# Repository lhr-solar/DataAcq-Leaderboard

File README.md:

# DataAcquisitionLeaderPCB

This PCB is designed for our solar vehicle to collect electrical and mechanical sensor data and transmit it wirelessly via LTE for real-time access. It also includes a GPS module for location tracking and an RF module as a backup communication system.

## LED Descriptions

LTE LEDs:

* HB (D7): Heartbeat.
  * Blinking = Our code is running on module.
* RSSI (D5): Received Singal Strength Integrity.
  * PWM based on strength (brighter = better).
* CONN (D4): Connection Indicator.
  * On, solid = Not connected.
  * 1/2 sec period blink = Last transmit failed.
  * 1 sec blink period = Normal operation.
* ON (D6): On.
  * On = Module is on.

RF LEDs:

* COM (D1): Commissioning (associate) status.
  * Blinking = Device is powered and operating properly.
  * Off = Device is alseep.
  * Note: blinks with certain patterns depending on number of RF_COM button presses (see datasheet).
* ON (D2): On.
  * On = Module is on.
* RSSI (D3): Received Singal Strength Integrity.
  * PWM based on strength (brighter = better).

GPS LED:

* NFX (D8): Negative 3D Fix.
  * Blinking (2 sec period) = Searching for satellites, no position fix.
  * Off = Acquired satellite signal.

## Testpoint Descriptions

LTE Testpoints:

* UART5 (J3)
  * Pin 3 TX = Transmit
  * Pin 2 RX = Receive
  * Pin 1 NR = Negative Reset (Note: this is not a UART singal, it is the module NRESET singal)

* Test Trace (J4)
  * Provides access to 4 pins (traces) to help in debugging code on the LTE module.

RF Testpoints:

* UART2 (J2)
  * Pin 3 TX = Transmit
  * Pin 2 RX = Receive
  * Pin 1 NR = Negative Reset (Note: this is not a UART singal, it is the module NRESET singal)

GPS Testpoints:

* I2C (J5)
  * Pin 3 SDA = Serial Data
  * Pin 2 SCL = Serial Clock
  * Pin 1 NR = Negative Reset (Note: this is not a I2C singal, it is the module NRESET singal)

## Pushbutton Descriptions

LTE_RESET: When pressed LTE module resets.
GPS_RESET: When pressed GPS module resets.
RF_RESET: When pressed RF module resets.
RF_COM: RF Commissioning button (see datasheet).

## PCB

## Schematic

[PDF](DataAcqLeaderBoard_Schematic.pdf)

## BOM

[BOM](DataAcqLeaderBoard/bom/bom.csv)
[IBOM](DataAcqLeaderBoard/bom/ibom.html)
[Mouser Cart](https://www.mouser.com/ProjectManager/ProjectDetail.aspx?AccessID=583e28cb45)

Cart does not include: 

  - [GPS Ferite Bead](https://www.digikey.com/en/products/detail/pulse-electronics/GMLB-100505-0600A-N8/12417638)
  - [GPS Module]( https://www.adafruit.com/product/790?gad_source=1&gclid=Cj0KCQiAsaS7BhDPARIsAAX5cSBvdF13g1xnso75e2ID2pkFIsjjoOZ1HywqQ3y7T4lSuiXb9zWTkFsaAgU-EALw_wcB)
  - [Digi XBee LTE Module](https://www.digi.com/products/embedded-systems/digi-xbee/cellular-modems/digi-xbee-3-global-lte-cat-4#partnumbers )
  - [Digi XBee RF Module](https://www.digi.com/products/embedded-systems/digi-xbee/rf-modules/sub-1-ghz-rf-modules/digi-xbee-xr-900#partnumbers)

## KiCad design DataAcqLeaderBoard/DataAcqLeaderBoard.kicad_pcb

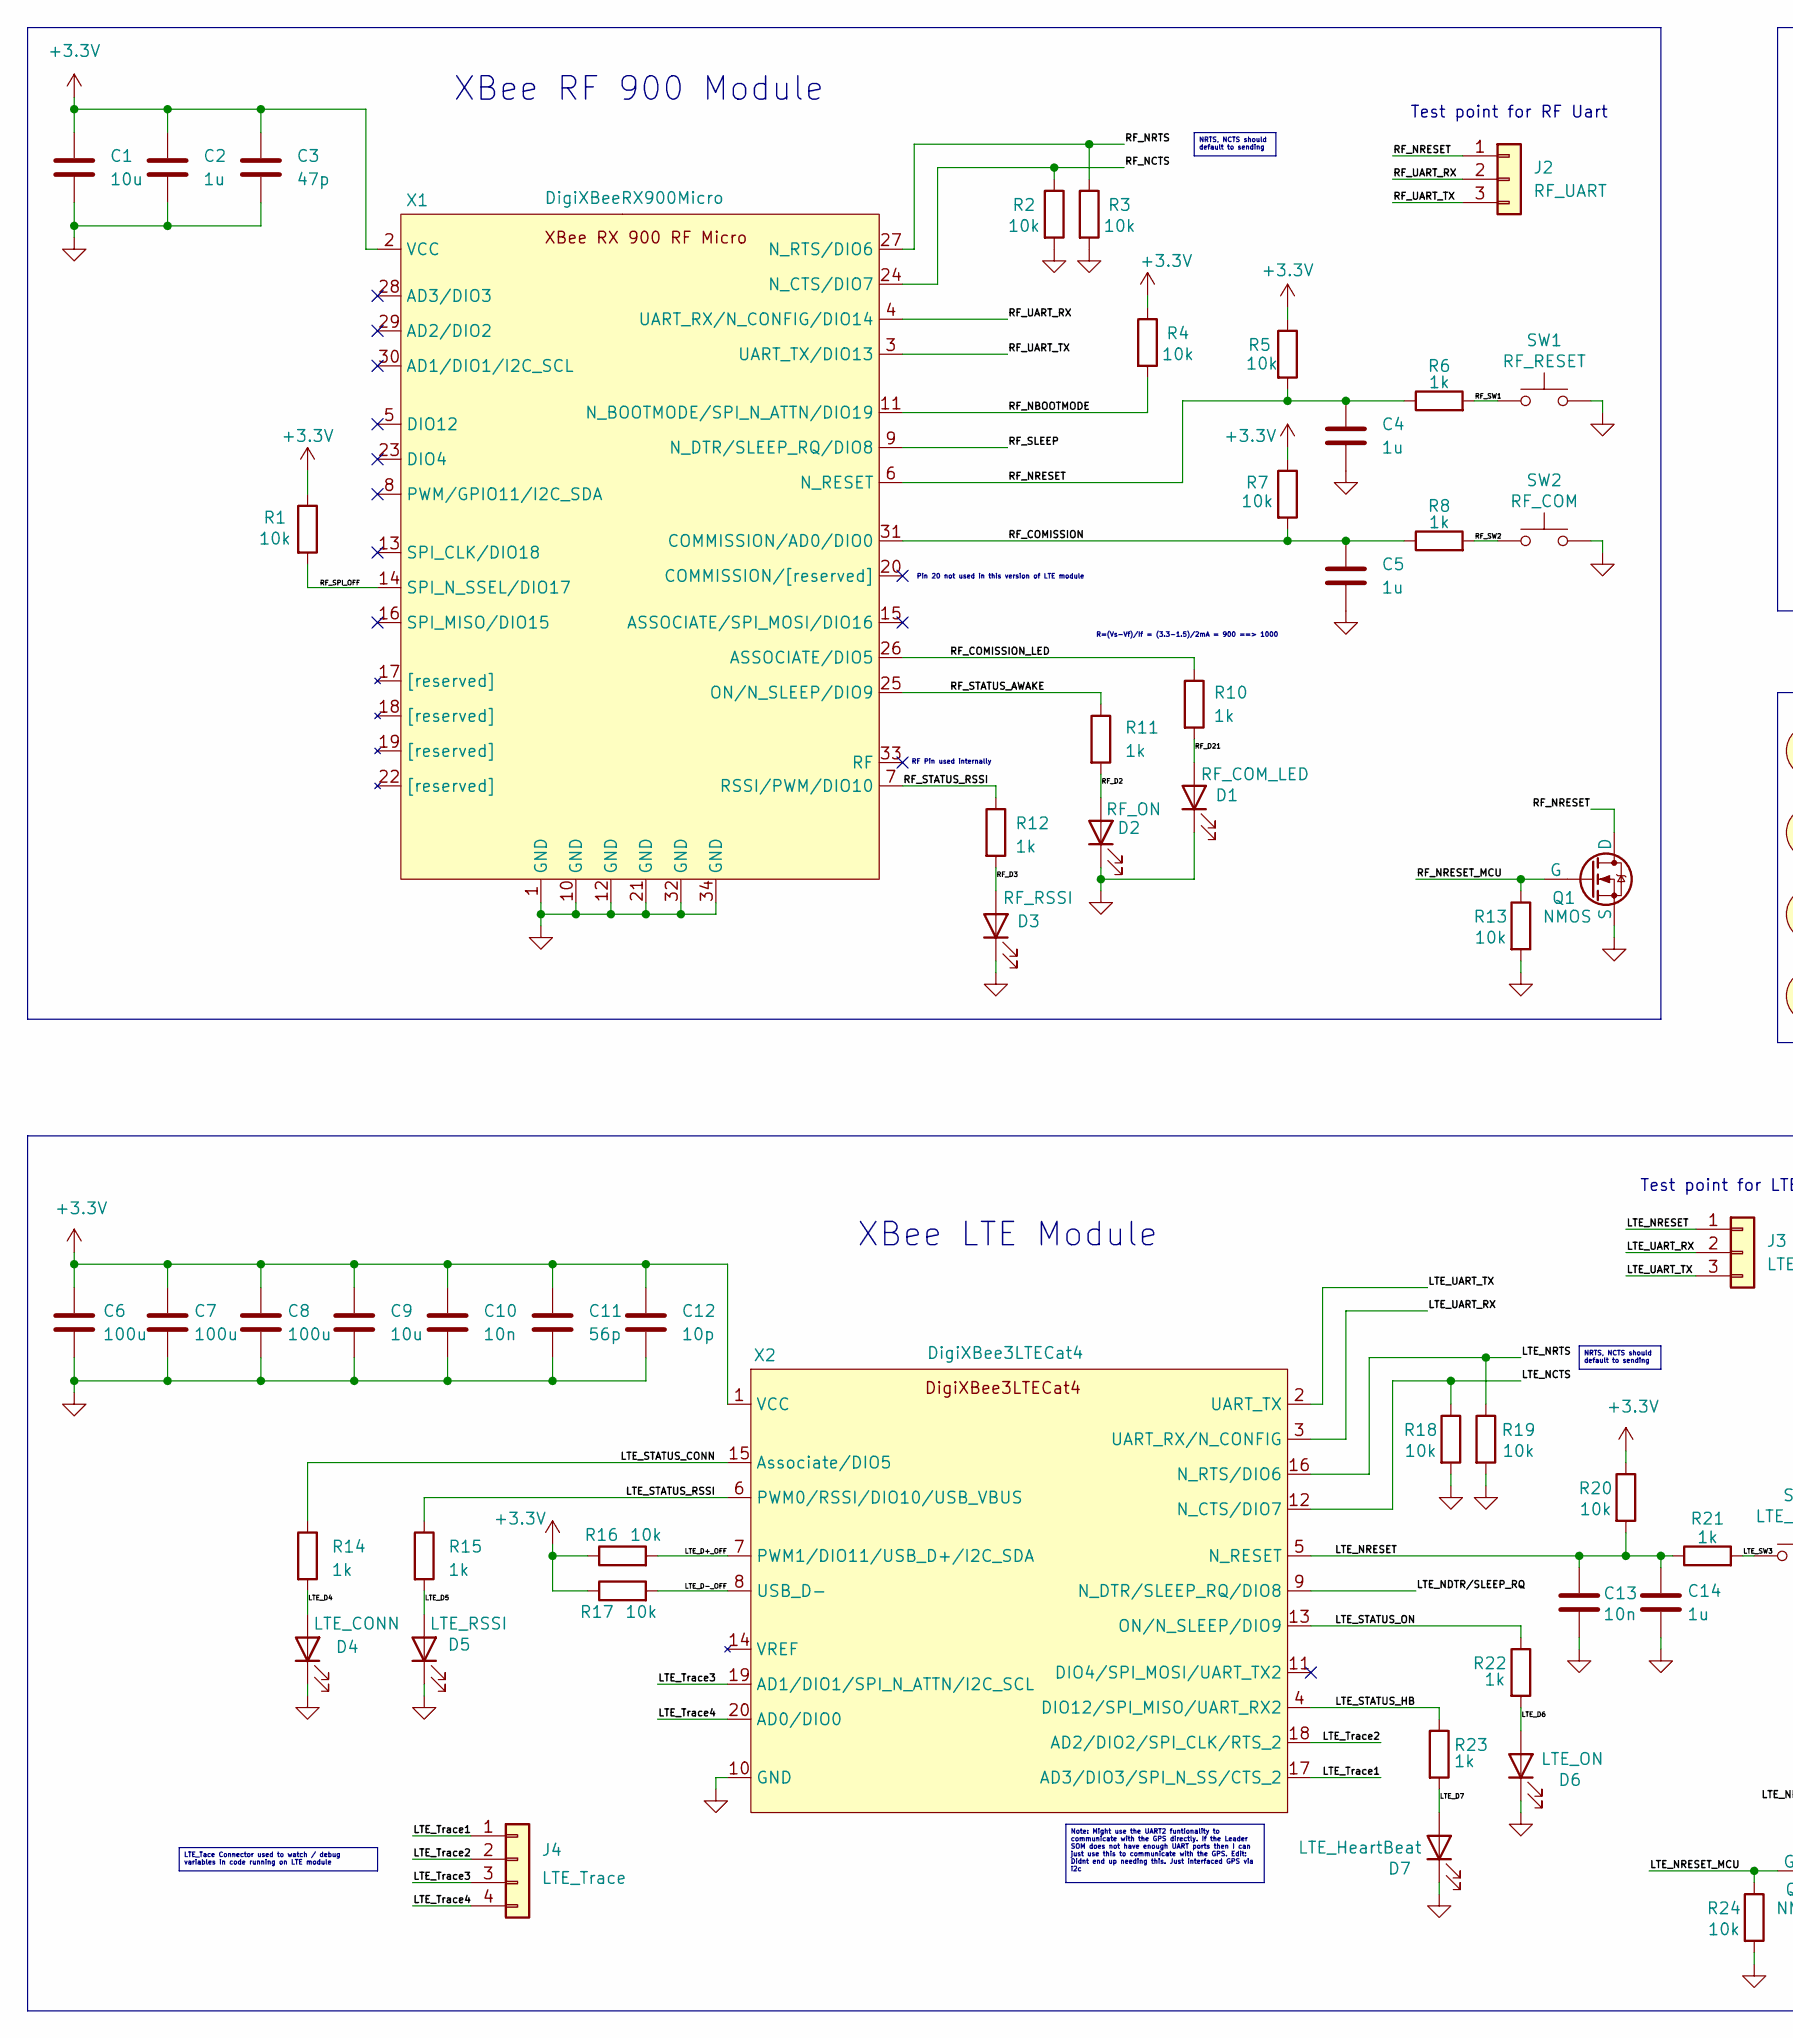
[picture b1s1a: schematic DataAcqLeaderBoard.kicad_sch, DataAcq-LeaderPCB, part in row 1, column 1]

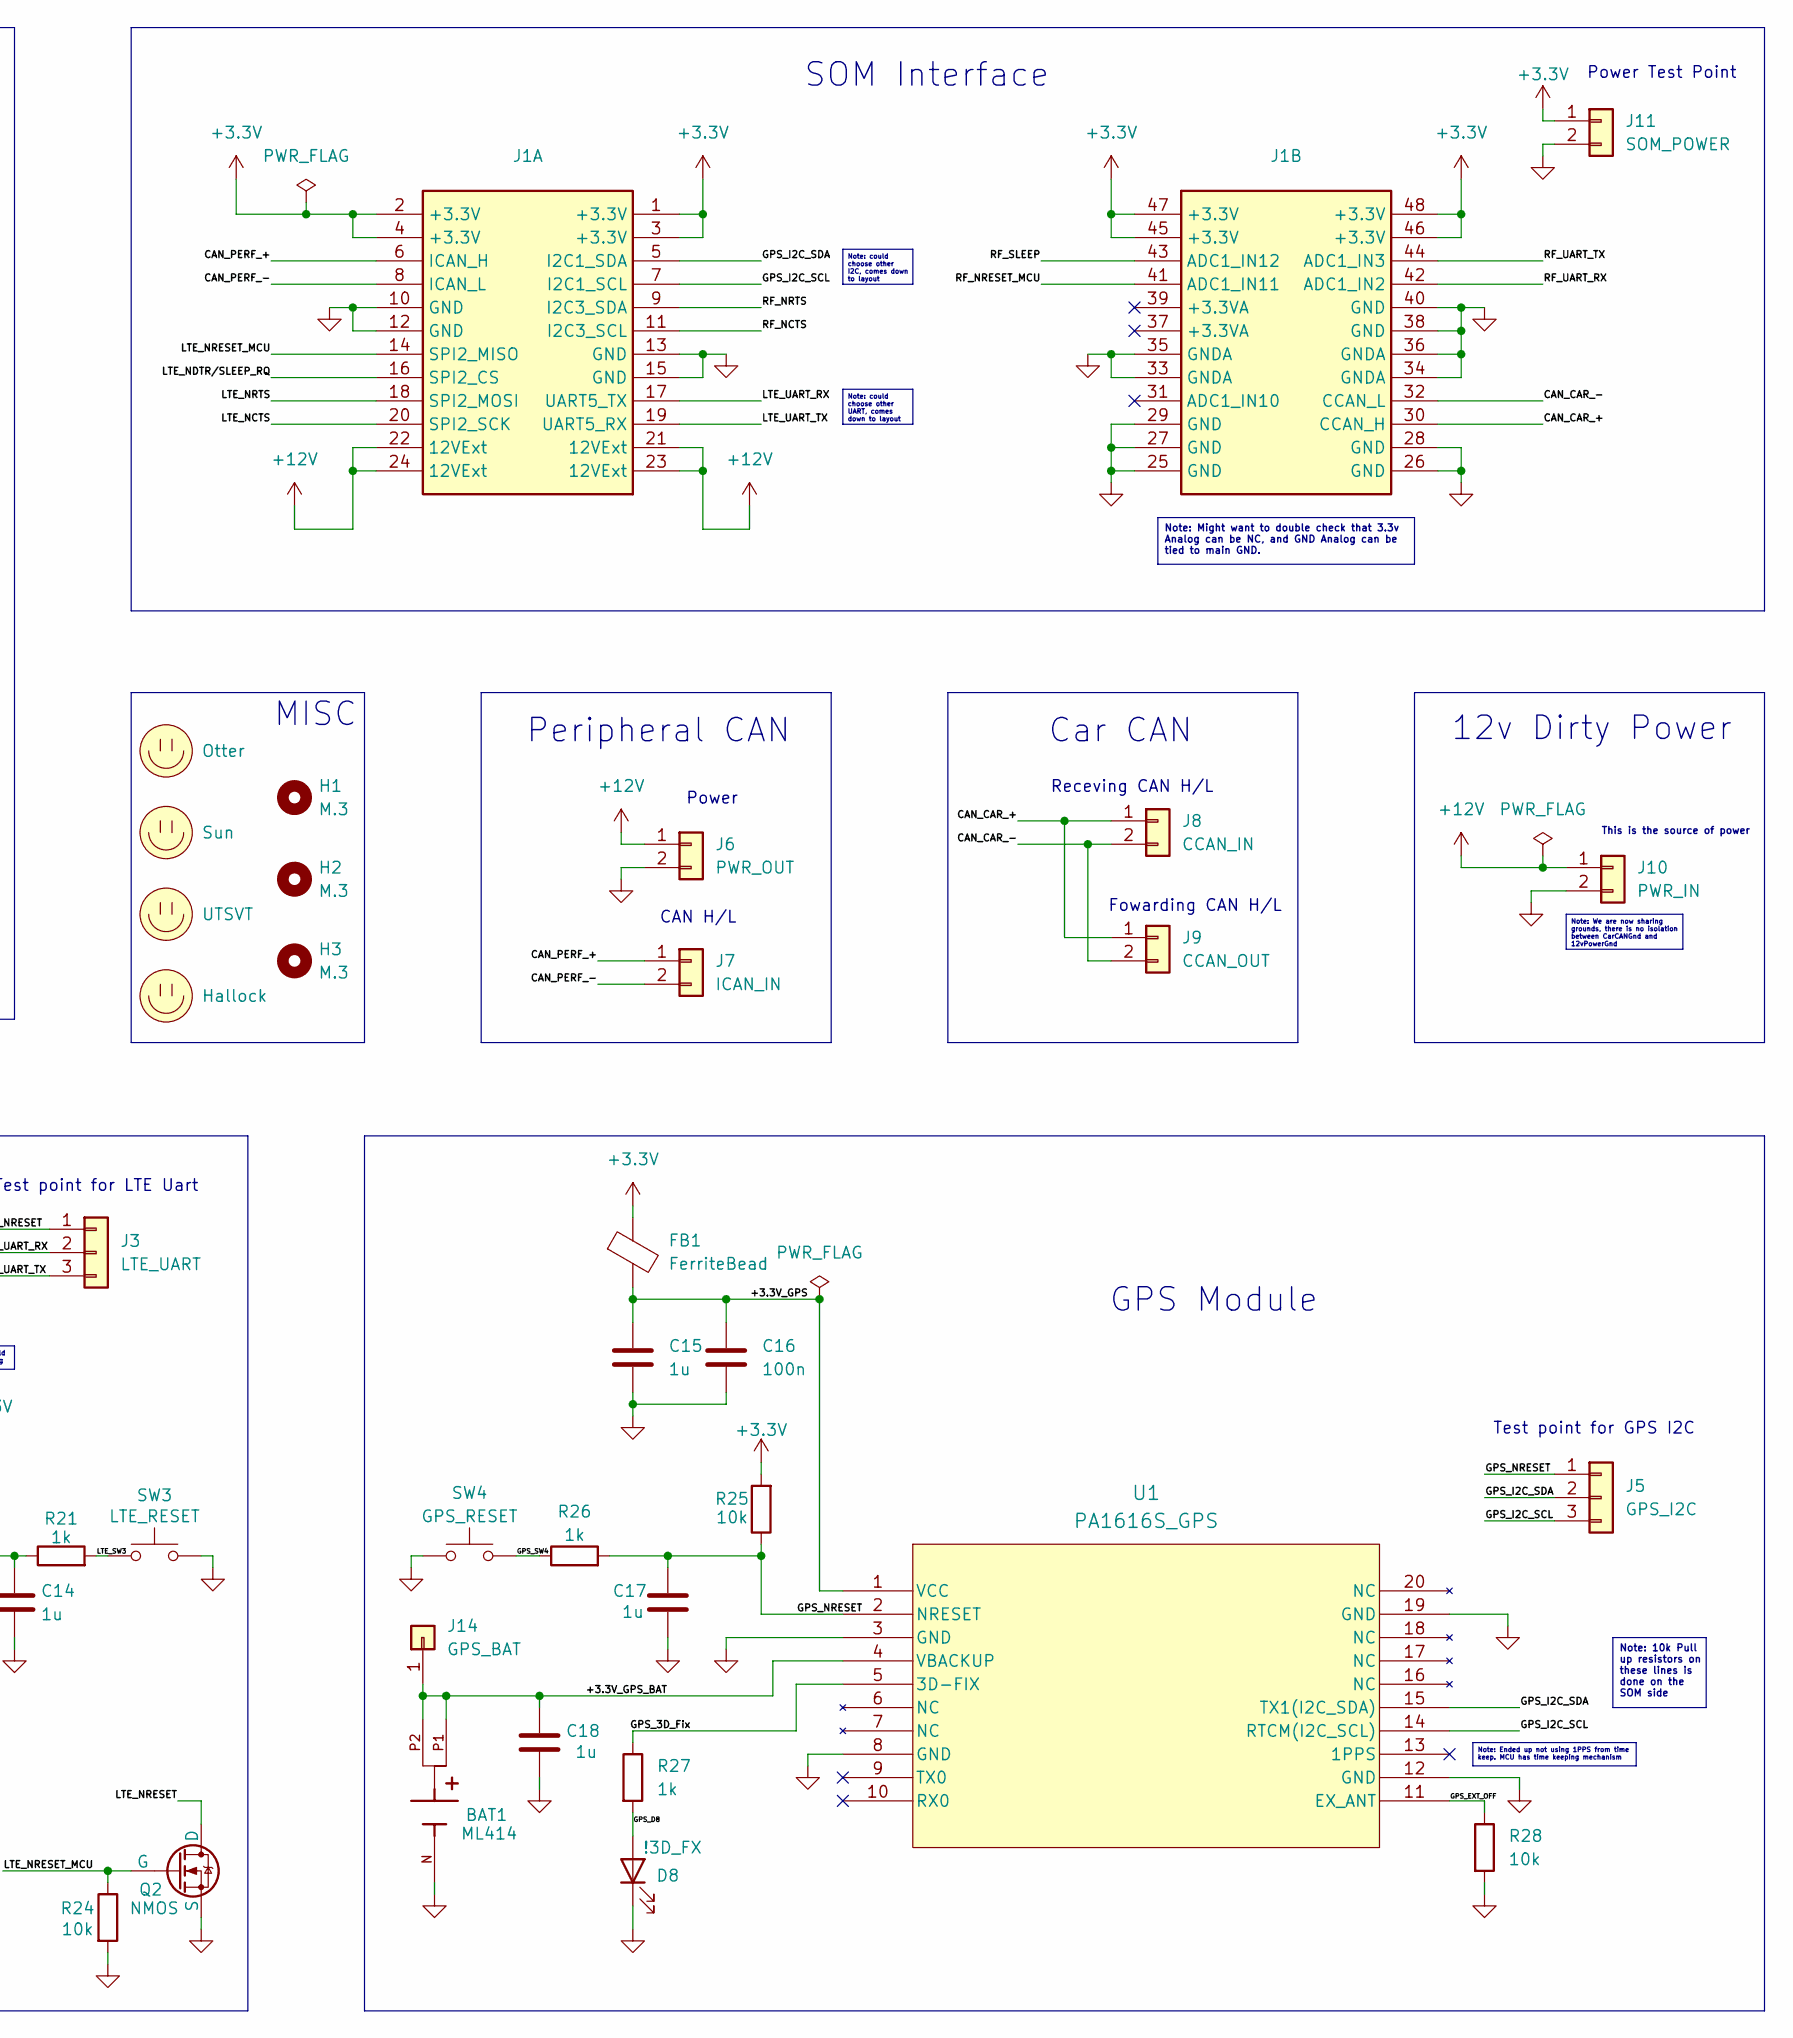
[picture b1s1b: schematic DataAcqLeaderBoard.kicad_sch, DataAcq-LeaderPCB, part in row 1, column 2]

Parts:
BAT1: ML414; BAT_2994TR; Mouser Part Number 534-2994TR
C1, C9: 10u; C_0805_2012Metric; Mouser Part Number 755-TCP0J106M8R
C2, C4, C5, C14, C15, C17, C18: 1u; C_0805_2012Metric; Mouser Part Number 80-C0805C105J4RACLR
C3: 47p; C_0805_2012Metric; Mouser Part Number 80-C0805C470F5G
C6, C7, C8: 100u; C_0805_2012Metric; Mouser Part Number 755-TCTPL0G107M8R-V1
C10, C13: 10n; C_0805_2012Metric; Mouser Part Number 80-C0805C103F8HAUTO
C11: 56p; C_0805_2012Metric; Mouser Part Number 80-C0805C560FBG
C12: 10p; C_0805_2012Metric; Mouser Part Number 80-C0805C100F1GACTU
C16: 100n; C_0805_2012Metric; Mouser Part Number 80-C0805C104M5R
D1: RF_COM_LED; LED_0805_2012Metric; Mouser Part Number 604-APTD2012LCGCK
D2: RF_ON; LED_0805_2012Metric; Mouser Part Number 604-APTD2012LCGCK
D3: RF_RSSI; LED_0805_2012Metric; Mouser Part Number 604-APTD2012LCGCK
D4: LTE_CONN; LED_0805_2012Metric; Mouser Part Number 604-APTD2012LCGCK
D5: LTE_RSSI; LED_0805_2012Metric; Mouser Part Number 604-APTD2012LCGCK
D6: LTE_ON; LED_0805_2012Metric; Mouser Part Number 604-APTD2012LCGCK
D7: LTE_HeartBeat; LED_0805_2012Metric; Mouser Part Number 604-APTD2012LCGCK
D8: !3D_FX; LED_0805_2012Metric; Mouser Part Number 604-APTD2012LCGCK
FB1: FerriteBead; R_0402_1005Metric
H1, H2, H3: M.3; MountingHole_3mm
J1: LeaderSOM; Mouser Part Number 538-53307-2471
J2: RF_UART; PinHeader_1x03_P2.54mm_Vertical; Mouser Part Number 538-22-28-4035
J3: LTE_UART; PinHeader_1x03_P2.54mm_Vertical; Mouser Part Number 538-22-28-4035
J4: LTE_Trace; PinHeader_1x04_P2.54mm_Vertical; Mouser Part Number 538-22-28-4045
J5: GPS_I2C; PinHeader_1x03_P2.54mm_Vertical; Mouser Part Number 538-22-28-4035
J6: PWR_OUT; CONN_SD-43650-006_02_MOL; Mouser Part Number 538-43650-0215
J7: ICAN_IN; CONN_SD-43650-006_02_MOL; Mouser Part Number 538-43650-0215
J8: CCAN_IN; CONN_SD-43650-006_02_MOL; Mouser Part Number 538-43650-0215
J9: CCAN_OUT; CONN_SD-43650-006_02_MOL; Mouser Part Number 538-43650-0215
J10: PWR_IN; CONN_SD-43650-006_02_MOL; Mouser Part Number 538-43650-0215
J11: SOM_POWER; PinHeader_1x02_P2.54mm_Vertical
J14: GPS_BAT; TestPoint_HEX_3mmID
LOGO1: Otter; otter
LOGO2: UTSVT; UTSVT_Logo_Symbol
LOGO3: Sun; sun
LOGO4: Hallock; Hallock_Image_Tiny
Q1, Q2: NMOS; SOT-23-3; Mouser Part Number 942-IRLML0030TRPBF
R1, R2, R3, R4, R5, R7, R13, R16, R17, R18, R19, R20, R24, R25, R28: 10k; R_0805_2012Metric; Mouser Part Number 71-CRCW080510K0FKEAC
R6, R8, R10, R11, R12, R14, R15, R21, R22, R23, R26, R27: 1k; R_0805_2012Metric; Mouser Part Number 71-CRCW08051K00FKEAC
SW1: RF_RESET; SW_SPST_B3SL-1002P; Mouser Part Number 653-B3SL-1002P
SW2: RF_COM; SW_SPST_B3SL-1002P; Mouser Part Number 653-B3SL-1002P
SW3: LTE_RESET; SW_SPST_B3SL-1002P; Mouser Part Number 653-B3SL-1002P
SW4: GPS_RESET; SW_SPST_B3SL-1002P; Mouser Part Number 653-B3SL-1002P
U1: PA1616S_GPS; PA1616S_ADA
X1: DigiXBeeRX900Micro; XBeeXR900RFMicro
X2: DigiXBee3LTECat4

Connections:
+3.3V: C1.1, C2.1, C3.1, C6.1, C7.1, C8.1, C9.1, C10.1, C11.1, C12.1, FB1.1, J1.1 (+3.3V), J1.2 (+3.3V), J1.3 (+3.3V), J1.4 (+3.3V), J1.45 (+3.3V), J1.46 (+3.3V), J1.47 (+3.3V), J1.48 (+3.3V), J11.1, R1.1, R4.1, R5.1, R7.1, R16.1, R17.1, R20.1, R25.2, X1.2 (VCC), X2.1 (VCC)
+12V: J1.21 (12VExt), J1.22 (12VExt), J1.23 (12VExt), J1.24 (12VExt), J6.1, J10.1
/+3.3V_GPS: C15.1, C16.1, FB1.2, U1.1 (VCC)
/+3.3V_GPS_BAT: BAT1.P1, BAT1.P2, C18.1, J14.1, U1.4 (VBACKUP)
/CAN_CAR_+: J1.30 (CCAN_H), J8.1, J9.1
/CAN_CAR_-: J1.32 (CCAN_L), J8.2, J9.2
/CAN_PERF_+: J1.6 (ICAN_H), J7.1
/CAN_PERF_-: J1.8 (ICAN_L), J7.2
/GPS_3D_Fix: R27.1, U1.5 (3D-FIX)
/GPS_D8: D8.2 (A), R27.2
/GPS_EXT_OFF: R28.1, U1.11 (EX_ANT)
/GPS_I2C_SCL: J1.7 (I2C1_SCL), J5.3, U1.14 (RTCM(I2C_SCL))
/GPS_I2C_SDA: J1.5 (I2C1_SDA), J5.2, U1.15 (TX1(I2C_SDA))
/GPS_NRESET: C17.1, J5.1, R25.1, R26.2, U1.2 (NRESET)
/GPS_SW4: R26.1, SW4.2
/LTE_D4: D4.2 (A), R14.2
/LTE_D5: D5.2 (A), R15.2
/LTE_D6: D6.2 (A), R22.2
/LTE_D7: D7.2 (A), R23.2
/LTE_D+_OFF: R16.2, X2.7 (PWM1/DIO11/USB_D+/I2C_SDA)
/LTE_D-_OFF: R17.2, X2.8 (USB_D-)
/LTE_NCTS: J1.20 (SPI2_SCK), R18.1, X2.12 (N_CTS/DIO7)
/LTE_NDTR/SLEEP_RQ: J1.16 (SPI2_CS), X2.9 (N_DTR/SLEEP_RQ/DIO8)
/LTE_NRESET: C13.1, C14.1, J3.1, Q2.1 (D), R20.2, R21.1, X2.5 (N_RESET)
/LTE_NRESET_MCU: J1.14 (SPI2_MISO), Q2.2 (G), R24.1
/LTE_NRTS: J1.18 (SPI2_MOSI), R19.1, X2.16 (N_RTS/DIO6)
/LTE_STATUS_CONN: R14.1, X2.15 (Associate/DIO5)
/LTE_STATUS_HB: R23.1, X2.4 (DIO12/SPI_MISO/UART_RX2)
/LTE_STATUS_ON: R22.1, X2.13 (ON/N_SLEEP/DIO9)
/LTE_STATUS_RSSI: R15.1, X2.6 (PWM0/RSSI/DIO10/USB_VBUS)
/LTE_SW3: R21.2, SW3.1
/LTE_Trace1: J4.1, X2.17 (AD3/DIO3/SPI_N_SS/CTS_2)
/LTE_Trace2: J4.2, X2.18 (AD2/DIO2/SPI_CLK/RTS_2)
/LTE_Trace3: J4.3, X2.19 (AD1/DIO1/SPI_N_ATTN/I2C_SCL)
/LTE_Trace4: J4.4, X2.20 (AD0/DIO0)
/LTE_UART_RX: J1.17 (UART5_TX), J3.2, X2.3 (UART_RX/N_CONFIG)
/LTE_UART_TX: J1.19 (UART5_RX), J3.3, X2.2 (UART_TX)
/RF_COMISSION: C5.1, R7.2, R8.1, X1.31 (COMMISSION/AD0/DIO0)
/RF_COMISSION_LED: R10.1, X1.26 (ASSOCIATE/DIO5)
/RF_D2: D2.2 (A), R11.2
/RF_D3: D3.2 (A), R12.2
/RF_D21: D1.2 (A), R10.2
/RF_NBOOTMODE: R4.2, X1.11 (N_BOOTMODE/SPI_N_ATTN/DIO19)
/RF_NCTS: J1.11 (I2C3_SCL), R2.1, X1.24 (N_CTS/DIO7)
/RF_NRESET: C4.1, J2.1, Q1.1 (D), R5.2, R6.1, X1.6 (N_RESET)
/RF_NRESET_MCU: J1.41 (ADC1_IN11), Q1.2 (G), R13.1
/RF_NRTS: J1.9 (I2C3_SDA), R3.1, X1.27 (N_RTS/DIO6)
/RF_SLEEP: J1.43 (ADC1_IN12), X1.9 (N_DTR/SLEEP_RQ/DIO8)
/RF_SPI_OFF: R1.2, X1.14 (SPI_N_SSEL/DIO17)
/RF_STATUS_AWAKE: R11.1, X1.25 (ON/N_SLEEP/DIO9)
/RF_STATUS_RSSI: R12.1, X1.7 (RSSI/PWM/DIO10)
/RF_SW1: R6.2, SW1.1
/RF_SW2: R8.2, SW2.1
/RF_UART_RX: J1.42 (ADC1_IN2), J2.2, X1.4 (UART_RX/N_CONFIG/DIO14)
/RF_UART_TX: J1.44 (ADC1_IN3), J2.3, X1.3 (UART_TX/DIO13)
GND: BAT1.N, C1.2, C2.2, C3.2, C4.2, C5.2, C6.2, C7.2, C8.2, C9.2, C10.2, C11.2, C12.2, C13.2, C14.2, C15.2, C16.2, C17.2, C18.2, D1.1 (K), D2.1 (K), D3.1 (K), D4.1 (K), D5.1 (K), D6.1 (K), D7.1 (K), D8.1 (K), J1.10 (GND), J1.12 (GND), J1.13 (GND), J1.15 (GND), J1.25 (GND), J1.26 (GND), J1.27 (GND), J1.28 (GND), J1.29 (GND), J1.33 (GNDA), J1.34 (GNDA), J1.35 (GNDA), J1.36 (GNDA), J1.38 (GND), J1.40 (GND), J6.2, J10.2, J11.2, Q1.3 (S), Q2.3 (S), R2.2, R3.2, R13.2, R18.2, R19.2, R24.2, R28.2, SW1.2, SW2.2, SW3.2, SW4.1, U1.3 (GND), U1.8 (GND), U1.12 (GND), U1.19 (GND), X1.1 (GND), X1.10 (GND), X1.12 (GND), X1.21 (GND), X1.32 (GND), X1.34 (GND), X2.10 (GND)

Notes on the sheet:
NRTS, NCTS should default to sending
Note: could choose other UART, comes down to layout
Note: Might want to double check that 3.3v Analog can be NC, and GND Analog can be tied to main GND.
Note: 10k Pull up resistors on these lines is done on the SOM side
LTE_Tace Connector used to watch / debug variables in code running on LTE module
Note: Ended up not using 1PPS from time keep. MCU has time keeping mechanism
Note: We are now sharing grounds, there is no isolation between CarCANGnd and 12vPowerGnd
Note: could choose other I2C, comes down to layout
Note: Might use the UART2 funtionality to communicate with the GPS directly. If the Leader SOM does not have enough UART ports then I can just use this to communicate with the GPS. Edit: Didnt end up needing this. Just interfaced GPS via i2c
Test point for LTE Uart
This is the source of power
Test point for RF Uart
Pin 20 not used in this version of LTE module
XBee LTE Module
12v Dirty Power
Receving CAN H/L
Test point for GPS I2C
MISC
Power Test Point
Car CAN
GPS Module
CAN H/L
RF Pin used internally
Fowarding CAN H/L
XBee RF 900 Module
R=(Vs-Vf)/If = (3.3-1.5)/2mA = 900 ==> 1000
Power
Peripheral CAN
SOM Interface

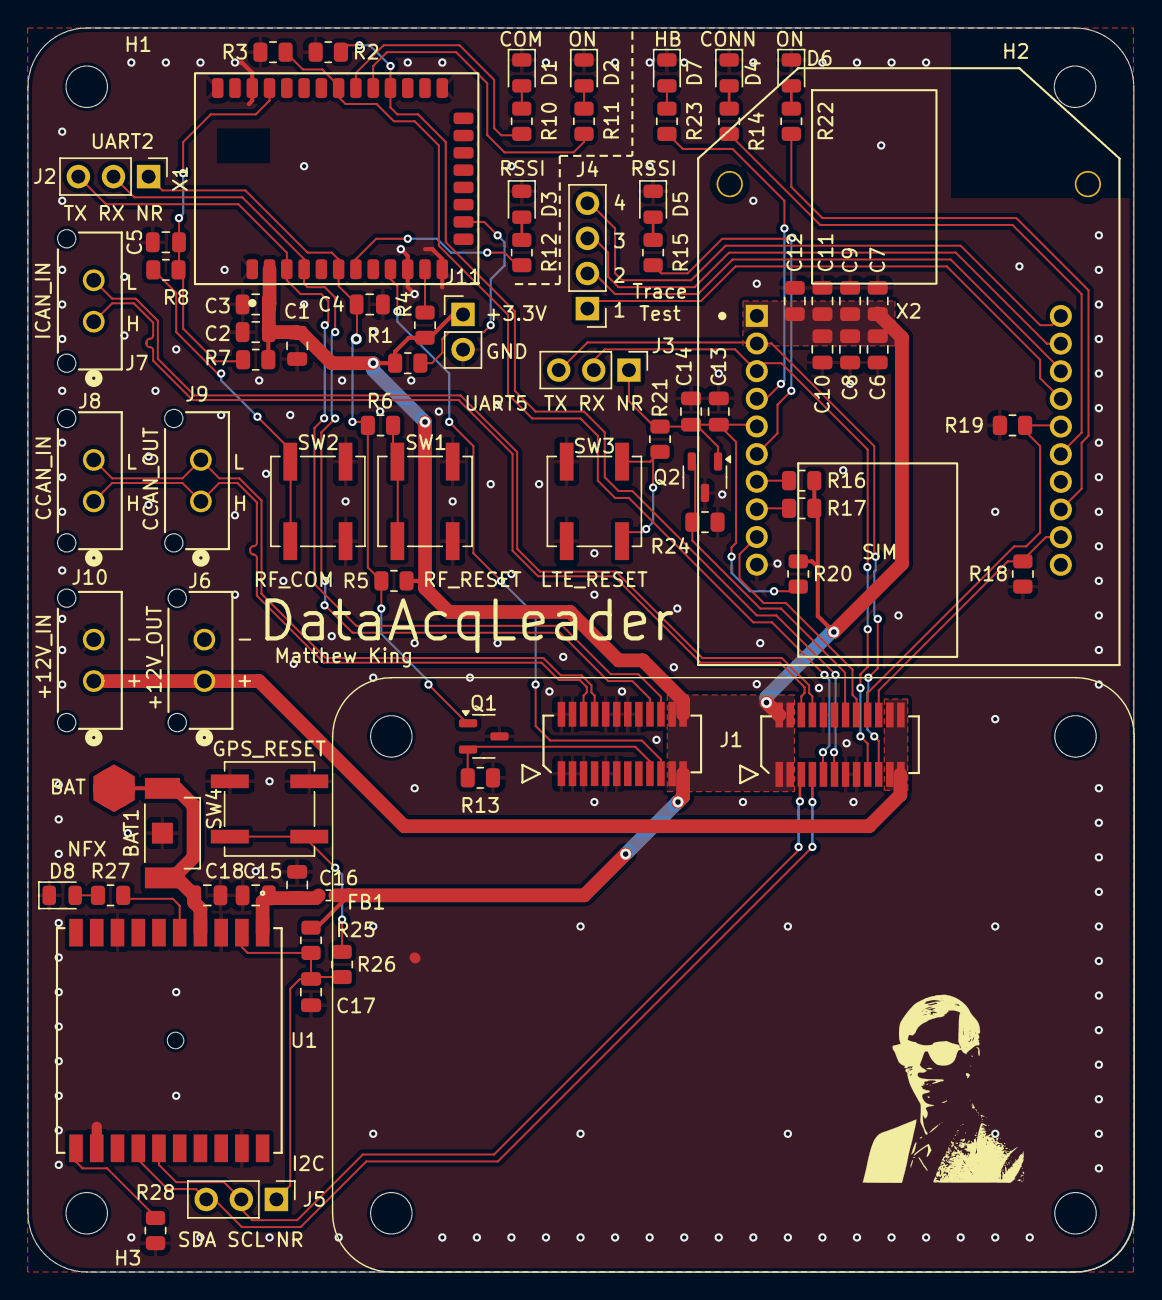
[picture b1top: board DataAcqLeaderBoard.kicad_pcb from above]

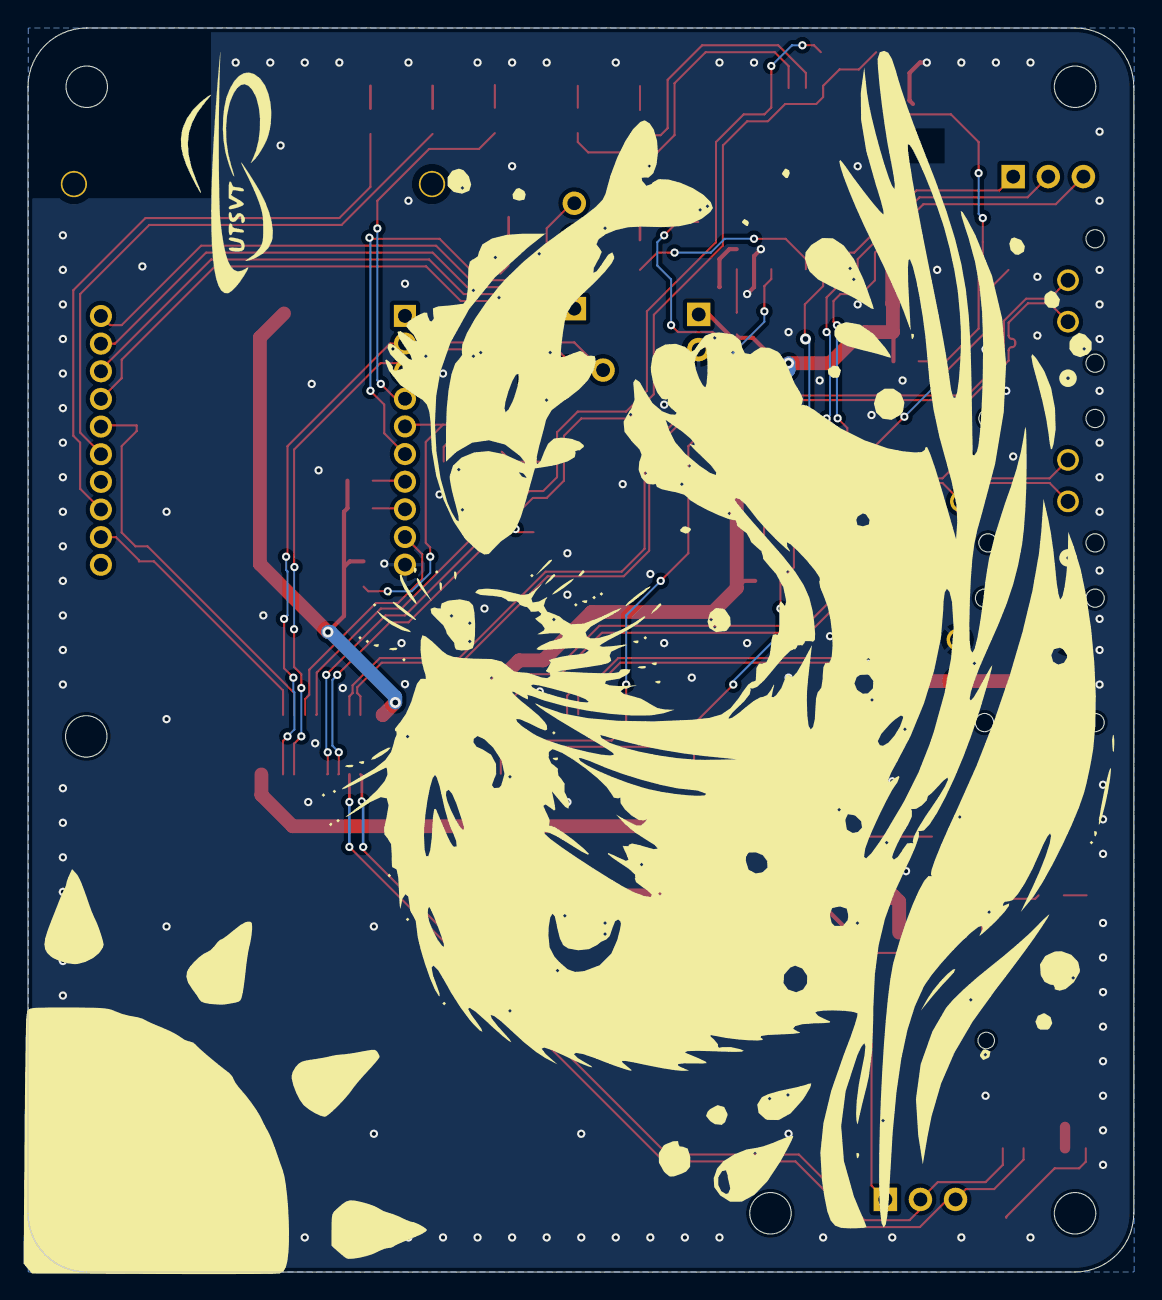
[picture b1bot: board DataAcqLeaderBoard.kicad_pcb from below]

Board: 2 copper layers, 80.0 x 90.0 mm, 83 parts (3 on the bottom side), 56 nets.

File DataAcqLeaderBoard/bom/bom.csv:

"#","Reference","Value","Qty","Footprint","Datasheet","P/N","Mouser Part Number","Link","DNP"
"1","BAT1","ML414","1","DataAcqLeaderBoard-Footprints:BAT_2994TR","https://www.mouser.com/ProductDetail/Keystone-Electronics/29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","2994TR","534-2994TR","https://www.mouser.com/ProductDetail/Keystone-Electronics/29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",""
"2","C1,C9","10u","2","Capacitor_SMD:C_0805_2012Metric","~","TCP0J106M8R ","755-TCP0J106M8R ","https://www.mouser.com/ProductDetail/KYOCERA-AVX/TCP0J106M8R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",""
"3","C2,C4,C5,C14,C15,C17,C18","1u","7","Capacitor_SMD:C_0805_2012Metric","~","C0805C105J4RAC7210","80-C0805C105J4RACLR ","https://www.mouser.com/ProductDetail/KEMET/C0805C105J4RAC721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",""
"4","C3","47p","1","Capacitor_SMD:C_0805_2012Metric","~","C0805C470F5GACTU","80-C0805C470F5G ","https://www.mouser.com/ProductDetail/KEMET/C0805C470F5GACTU?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",""
"5","C6,C7,C8","100u","3","Capacitor_SMD:C_0805_2012Metric","~","TCTPL0G107M8R-V1 ","755-TCTPL0G107M8R-V1 ","https://www.mouser.com/ProductDetail/KYOCERA-AVX/TCTPL0G107M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",""
"6","C10,C13","10n","2","Capacitor_SMD:C_0805_2012Metric","~","C0805C103F8HACAUTO ","80-C0805C103F8HAUTO ","https://www.mouser.com/ProductDetail/KEMET/C0805C103F8HACAUT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",""
"7","C11","56p","1","Capacitor_SMD:C_0805_2012Metric","~","C0805C560FBGACTU","80-C0805C560FBG ","https://www.mouser.com/ProductDetail/KEMET/C0805C560FBGACTU?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",""
"8","C12","10p","1","Capacitor_SMD:C_0805_2012Metric","~","C0805C100F1GACTU","80-C0805C100F1GACTU ","https://www.mouser.com/ProductDetail/KEMET/C0805C100F1GACTU?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",""
"9","C16","100n","1","Capacitor_SMD:C_0805_2012Metric","~","C0805C104M5RACTU","80-C0805C104M5R ","https://www.mouser.com/ProductDetail/KEMET/C0805C104M5RACTU?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",""
"10","D1,D2,D3,D4,D5,D6,D7,D8","-- mixed values --","8","LED_SMD:LED_0805_2012Metric","","APTD2012LCGCK ","604-APTD2012LCGCK","https://www.mouser.com/ProductDetail/Kingbright/APTD2012LCGC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",""
"11","FB1","FerriteBead","1","Resistor_SMD:R_0402_1005Metric","~","GMLB-100505-0600A-N8 ","","https://www.digikey.com/en/products/detail/pulse-electronics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",""
"12","H1,H2,H3,LOGO1,LOGO2,LOGO3","-- mixed values --","6","-- mixed values --","-- mixed values --","","","",""
"13","J1","~","1","UTSVT_Special:LeaderSOM","https://www.molex.com/en-us/products/part-detail/533072471","53307-2471 ","538-53307-2471 ","https://www.mouser.com/ProductDetail/Molex/53307-2471?qs=3Dz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",""
"14","J2,J3,J5","-- mixed values --","3","Connector_PinHeader_2.54mm:PinHeader_1x03_P2.54mm_Vertical","~","22-28-4035 ","538-22-28-4035 ","https://www.mouser.com/ProductDetail/Molex/22-28-4035?qs=GAP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",""
"15","J4","LTE_Trace","1","Connector_PinHeader_2.54mm:PinHeader_1x04_P2.54mm_Vertical","~","22-28-4045 ","538-22-28-4045 ","https://www.mouser.com/ProductDetail/Molex/22-28-4045?qs=Muw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",""
"16","J6,J7,J8,J9,J10","-- mixed values --","5","DataAcqLeaderBoard-Footprints:CONN_SD-43650-006_02_MOL","~","43650-0215 ","538-43650-0215 ","https://www.mouser.com/ProductDetail/538-43650-0215",""
"17","Q1,Q2","NMOS","2","Package_TO_SOT_SMD:SOT-23-3","https://ngspice.sourceforge.io/docs/ngspice-html-manual/manu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","IRLML0030TRPBF","942-IRLML0030TRPBF ","https://www.mouser.com/ProductDetail/Infineon-Technologies/I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",""
"18","R1,R2,R3,R4,R5,R7,R13,R16,R17,R18,R19,R20,R24,R25,R28","10k","15","Resistor_SMD:R_0805_2012Metric","~","CRCW080510K0FKEA","71-CRCW080510K0FKEAC","https://www.mouser.com/ProductDetail/Vishay-Dale/CRCW080510K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",""
"19","R6,R8,R10,R11,R12,R14,R15,R21,R22,R23,R26,R27","1k","12","Resistor_SMD:R_0805_2012Metric","~","CRCW08051K00FKEAC","71-CRCW08051K00FKEAC","https://www.mouser.com/ProductDetail/Vishay-Dale/CRCW08051K0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",""
"20","SW1,SW2,SW3,SW4","-- mixed values --","4","Button_Switch_SMD:SW_SPST_B3SL-1002P","-- mixed values --","B3SL-1002P ","653-B3SL-1002P","https://www.mouser.com/ProductDetail/Omron-Electronics/B3SL-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",""
"21","U1","PA1616S_GPS","1","DataAcqLeaderBoard-Footprints:PA1616S_ADA","https://cdn-shop.adafruit.com/product-files/746/CD+PA1616S+D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","PA1616S","","https://www.adafruit.com/product/790?gad_source=1&gclid=Cj0K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",""
"22","X1","DigiXBeeRX900Micro","1","DataAcqLeaderBoard-Footprints:XBeeXR900RFMicro","https://fcc.report/FCC-ID/MCQ-XB9XR/7222310.pdf","XB-9XR-DMRM-001","","https://www.digi.com/products/embedded-systems/digi-xbee/rf-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",""
"23","X2","DigiXBee3LTECat4","1","DataAcqLeaderBoard-Footprints:DigiXBee3LTECat4","https://www.digi.com/resources/documentation/digidocs/PDFs/9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","XB3-C-G4-UT-001","","https://www.digi.com/products/embedded-systems/digi-xbee/cel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",""

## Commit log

2024-11-09 Inital comit
2024-11-09 Added GPS
2024-11-17 Added XBee RF Module
2024-11-18 Fixed RF Module's push buttons
2024-11-23 Fixed project paths and added .gitignore
2024-11-26 Actually fixed the symbol, footprint paths
2024-11-26 Removed old junk (symbol, footprint file setup)
2024-11-26 Rm more old stuff (backups and old path)
2024-11-27 Added Digi XBee LTE Module
2024-11-27 Debounced Push Buttons
2024-12-17 Added XBee RF and LTE Footprints
2024-12-19 Interfaced Leader SOM and added UTSVT Library
2024-12-20 First revision of schematic done
2024-12-23 Completed first draft of layout
2025-01-03 Updated Schematic, finished first rev of Layout
2025-01-06 Added README, added PCB dimensions
2025-01-10 Completed BOM & Filled out PR template
2025-01-19 Addressed PR comments (vias, test points, labels)
2025-01-19 Shifted GPS module down for more USB clearance
2025-01-19 Fixed CAN differential pair
